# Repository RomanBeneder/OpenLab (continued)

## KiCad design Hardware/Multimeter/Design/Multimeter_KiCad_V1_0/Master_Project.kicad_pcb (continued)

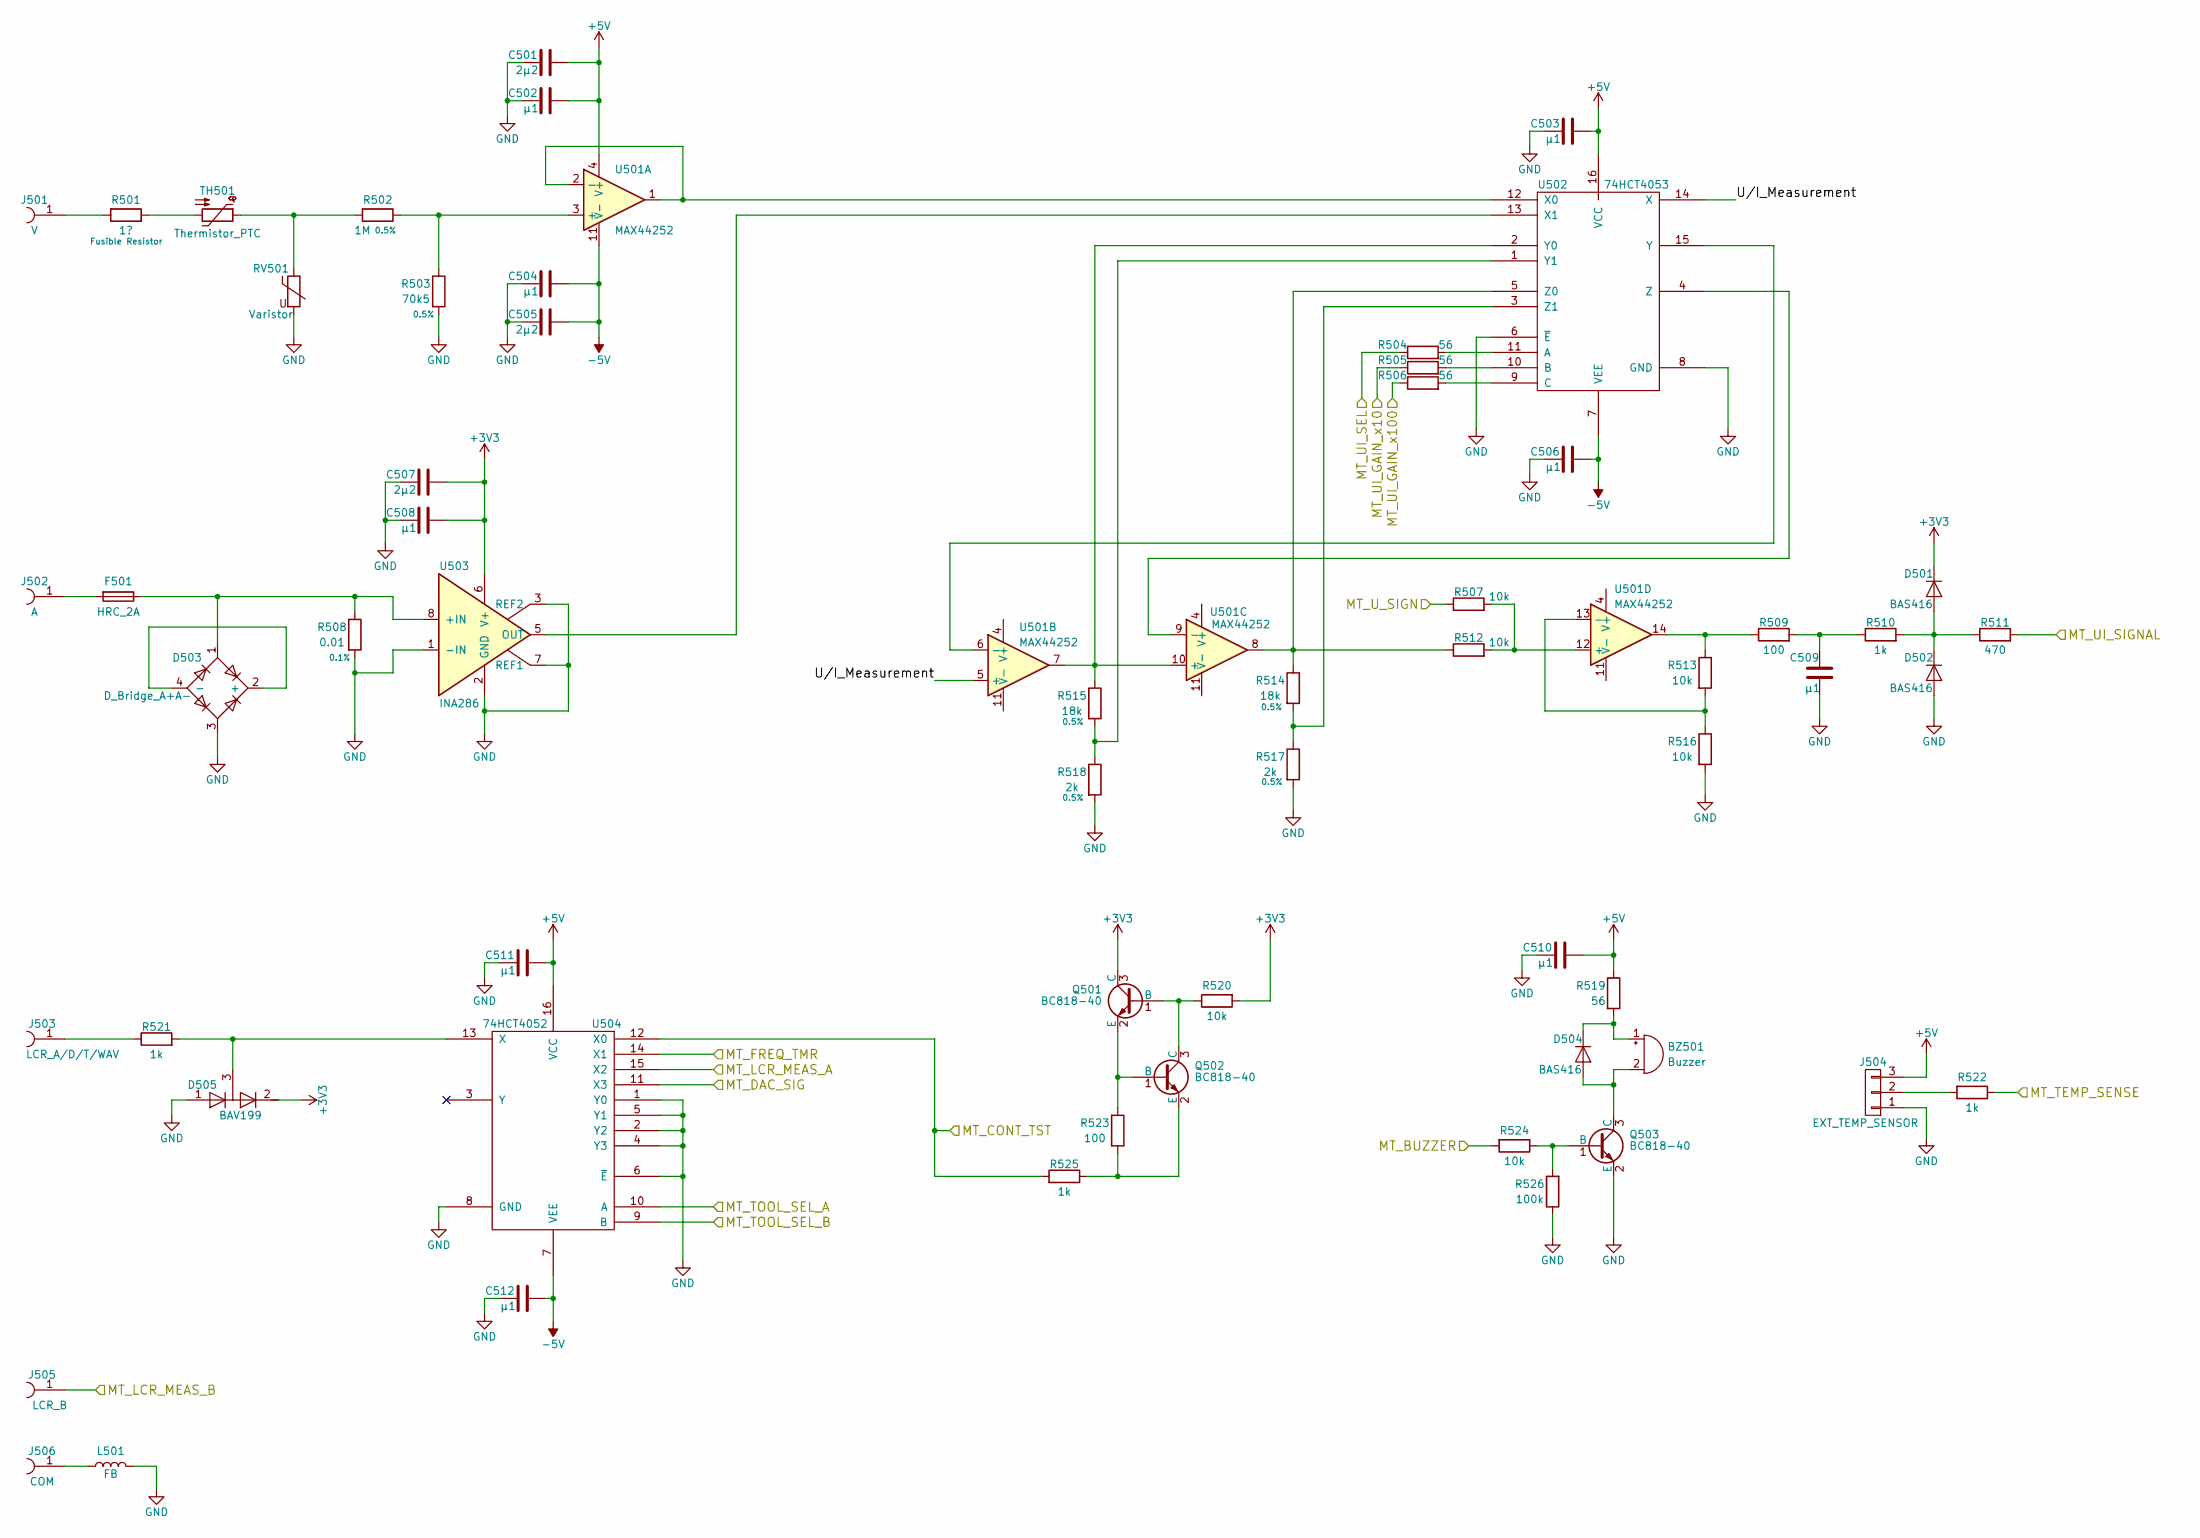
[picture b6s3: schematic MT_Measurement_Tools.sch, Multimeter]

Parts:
BZ501: Buzzer; MagneticBuzzer_ProSignal_ABT-410-RC
C501, C505, C507: 2µ2; C_0603
C502, C503, C504, C506, C508, C509, C510, C511, C512: µ1; C_0603
D501, D502, D504: BAS416; D_SOD-323
D503: D_Bridge_A+A-; Diode_Bridge_Round_D8.9mm
D505: BAV199; SOT-23
F501: HRC_2A; Fuseholder5x20_horiz_open_Schurter_0031_8201
J501: V; Banana_Jack_1Pin
J502: A; Banana_Jack_1Pin
J503: LCR_A/D/T/WAV; Banana_Jack_1Pin
J504: EXT_TEMP_SENSOR; Pin_Header_Straight_1x03_Pitch2.54mm
J505: LCR_B; Banana_Jack_1Pin
J506: COM; Banana_Jack_1Pin
L501: FB; R_0805
Q501, Q502, Q503: BC818-40; SOT-23
R501: 1?; R_Axial_DIN0207_L6.3mm_D2.5mm_P15.24mm_Horizontal
R502: 1M; R_0805; Toleranz 0.5%
R503: 70k5; R_0805; Toleranz 0.5%
R504, R505, R506, R519: 56; R_0603
R507, R512, R516, R520, R524: 10k; R_0603
R508: 0.01; R_4320; Toleranz 0.1%
R509, R523: 100; R_0603
R510, R521, R522, R525: 1k; R_0603
R511: 470; R_0603
R513: 10k; R_0603; Toleranz 1%
R514, R515: 18k; R_0603; Toleranz 0.5%
R517, R518: 2k; R_0603; Toleranz 0.5%
R526: 100k; R_0603
RV501: Varistor; RV_Disc_D7_W5.5_P5
TH501: Thermistor_PTC; R_Box_L14.4mm_W2.5mm_P5.08mm
U501: MAX44252; SOIC-14_3.9x8.7mm_Pitch1.27mm
U502: 74HCT4053; TSSOP-16_4.4x5mm_Pitch0.65mm
U503: INA286; SOIC-8_3.9x4.9mm_Pitch1.27mm
U504: 74HCT4052; TSSOP-16_4.4x5mm_Pitch0.65mm

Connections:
+3V3: C507.1, C508.1, D501.1 (K), D505.2 (K), Q501.3 (C), R520.2, U503.6 (V+); also elsewhere on the board
+5V: C501.1, C502.1, C503.1, C510.1, C511.1, J504.3, R519.1, U501.4 (V+), U502.16 (VCC), U504.16 (VCC); also elsewhere on the board
-5V: C504.1, C505.1, C506.1, C512.1, U501.11 (V-), U502.7 (VEE), U504.7 (VEE); also elsewhere on the board
/MT Measurement Tools/U/I_Measurement: U501.5 (+), U502.14 (X)
/TLD_BUZZER: R524.2; also elsewhere on the board
/TLD_CONT_TST: R525.2, U504.12 (X0); also elsewhere on the board
/TLD_DAC_SIG: U504.11 (X3); also elsewhere on the board
/TLD_FREQ_TMR: U504.14 (X1); also elsewhere on the board
/TLD_LCR_MEAS_A: U504.15 (X2); also elsewhere on the board
/TLD_LCR_MEAS_B: J505.1; also elsewhere on the board
/TLD_TEMP_SENSE: R522.1; also elsewhere on the board
/TLD_TOOL_SEL_A: U504.10 (A); also elsewhere on the board
/TLD_TOOL_SEL_B: U504.9 (B); also elsewhere on the board
/TLD_UI_GAIN_x10: R505.1; also elsewhere on the board
/TLD_UI_GAIN_x100: R506.1; also elsewhere on the board
/TLD_UI_SEL: R504.1; also elsewhere on the board
/TLD_UI_SIGNAL: R511.2; also elsewhere on the board
/TLD_U_SIGN: R507.1; also elsewhere on the board
GND: C501.2, C502.2, C503.2, C504.2, C505.2, C506.2, C507.2, C508.2, C509.1, C510.2, C511.2, C512.2, D502.2 (A), D503.3, D505.1 (A), J504.1, L501.2, Q503.2 (E), R503.2, R508.2, R516.2, R517.2, R518.2, R526.1, RV501.2, U502.6 (~E~), U502.8 (GND), U503.1 (-IN), U503.2 (GND), U503.3 (REF2), U503.7 (REF1), U504.1 (Y0), U504.2 (Y2), U504.4 (Y3), U504.5 (Y1), U504.6 (~E~), U504.8 (GND); also elsewhere on the board
unnamed: BZ501.1 (-), D504.1 (K), R519.2
unnamed: BZ501.2 (+), D504.2 (A), Q503.3 (C)
unnamed: C509.2, R509.2, R510.1
unnamed: D501.2 (A), D502.1 (K), R510.2, R511.1
unnamed: D503.1, F501.1, R508.1, U503.8 (+IN)
unnamed: D503.2 (+), D503.4 (-)
unnamed: D505.3 (common), R521.2, U504.13 (X)
unnamed: F501.2, J502.1
unnamed: J501.1, R501.2
unnamed: J503.1, R521.1
unnamed: J504.2, R522.2
unnamed: J506.1, L501.1
unnamed: Q501.1 (B), Q502.3 (C), R520.1
unnamed: Q501.2 (E), Q502.1 (B), R523.2
unnamed: Q502.2 (E), R523.1, R525.1
unnamed: Q503.1 (B), R524.1, R526.2
unnamed: R501.1, TH501.2
unnamed: R502.1, R503.1, U501.3 (+)
unnamed: R502.2, RV501.1, TH501.1
unnamed: R504.2, U502.11 (A)
unnamed: R505.2, U502.10 (B)
unnamed: R506.2, U502.9 (C)
unnamed: R507.2, R512.2, U501.12 (+)
unnamed: R509.1, R513.1, U501.14
unnamed: R512.1, R514.1, U501.8, U502.5 (Z0)
unnamed: R513.2, R516.1, U501.13 (-)
unnamed: R514.2, R517.1, U502.3 (Z1)
unnamed: R515.1, U501.7, U501.10 (+), U502.2 (Y0)
unnamed: R515.2, R518.1, U502.1 (Y1)
unnamed: U501.1, U501.2 (-), U502.12 (X0)
unnamed: U501.6 (-), U502.15 (Y)
unnamed: U501.9 (-), U502.4 (Z)
unnamed: U502.13 (X1), U503.5 (OUT)

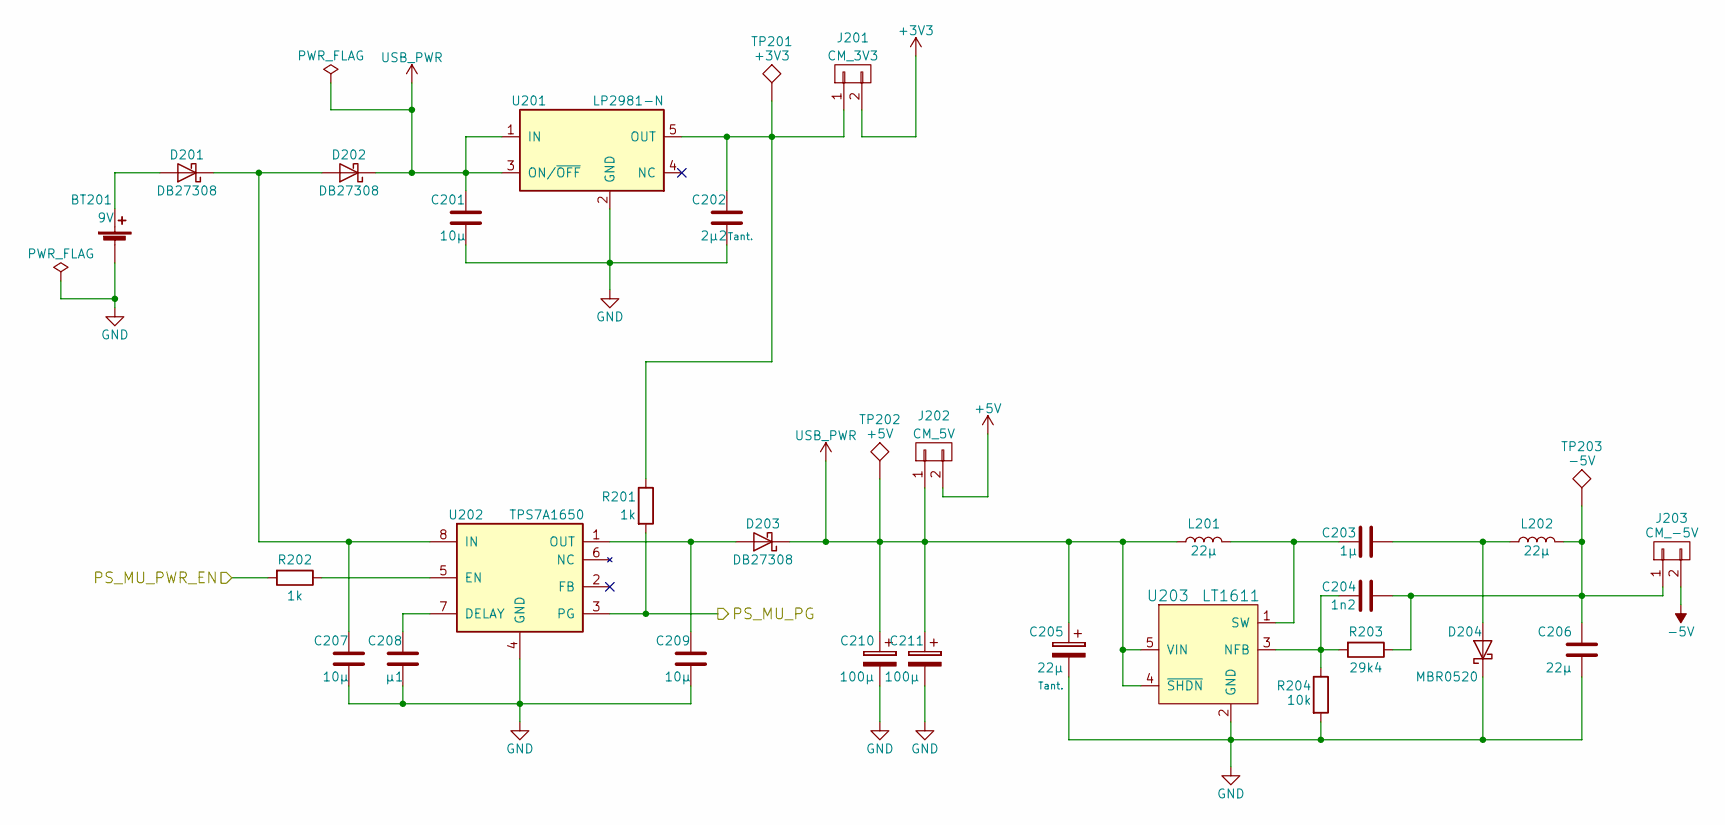
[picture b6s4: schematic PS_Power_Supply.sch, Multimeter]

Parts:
BT201: 9V; Pin_Header_Straight_1x02_Pitch2.54mm
C201, C207, C209: 10µ; C_1206
C202: 2µ2; C_1206
C203: 1µ; C_0603
C204: 1n2; C_0603
C205, C206: 22µ; C_1206
C208: µ1; C_0603
C210, C211: 100µ; CP_Elec_6.3x5.7
D201, D202, D203: DB27308; D_0603
D204: MBR0520; D_SOD-123
J201: CM_3V3; Pin_Header_Straight_1x02_Pitch2.54mm
J202: CM_5V; Pin_Header_Straight_1x02_Pitch2.54mm
J203: CM_-5V; Pin_Header_Straight_1x02_Pitch2.54mm
L201, L202: 22µ; Inductor_Taiyo-Yuden_MD-4040
R201, R202: 1k; R_0603
R203: 29k4; R_0603
R204: 10k; R_0603
TP201: +3V3; Measurement_Point_Square-SMD-Pad_Small
TP202: +5V; Measurement_Point_Square-SMD-Pad_Small
TP203: -5V; Measurement_Point_Square-SMD-Pad_Small
U201: LP2981-N; SOT-23-5
U202: TPS7A1650; TSSOP-8_3x3mm_Pitch0.65mm
U203: LT1611; SOT-23-5

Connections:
+3V3: J201.2; also elsewhere on the board
+5V: J202.2; also elsewhere on the board
-5V: J203.2; also elsewhere on the board
/TLD_MU_PG: R201.2, U202.3 (PG); also elsewhere on the board
/TLD_MU_PWR_EN: R202.2; also elsewhere on the board
GND: BT201.2 (-), C201.2, C202.2, C205.2, C206.1, C207.2, C208.2, C209.2, C210.2, C211.2, D204.1 (K), R204.2, U201.2 (GND), U202.4 (GND), U203.2 (GND); also elsewhere on the board
unnamed: BT201.1 (+), D201.2 (A)
unnamed: C202.1, J201.1, R201.1, TP201.1, U201.5 (OUT)
unnamed: C203.1, D204.2 (A), L202.1
unnamed: C203.2, L201.2, U203.1 (SW)
unnamed: C204.1, C206.2, J203.1, L202.2, R203.1, TP203.1
unnamed: C204.2, R203.2, R204.1, U203.3 (NFB)
unnamed: C207.1, D201.1 (K), D202.2 (A), U202.8 (IN)
unnamed: C208.1, U202.7 (DELAY)
unnamed: C209.1, D203.2 (A), U202.1 (OUT)
unnamed: R202.1, U202.5 (EN)
USB_PWR: C201.1, C205.1, C210.1, C211.1, D202.1 (K), D203.1 (K), J202.1, L201.1, TP202.1, U201.1 (IN), U201.3 (ON/~OFF~), U203.4 (~SHDN~), U203.5 (VIN); also elsewhere on the board

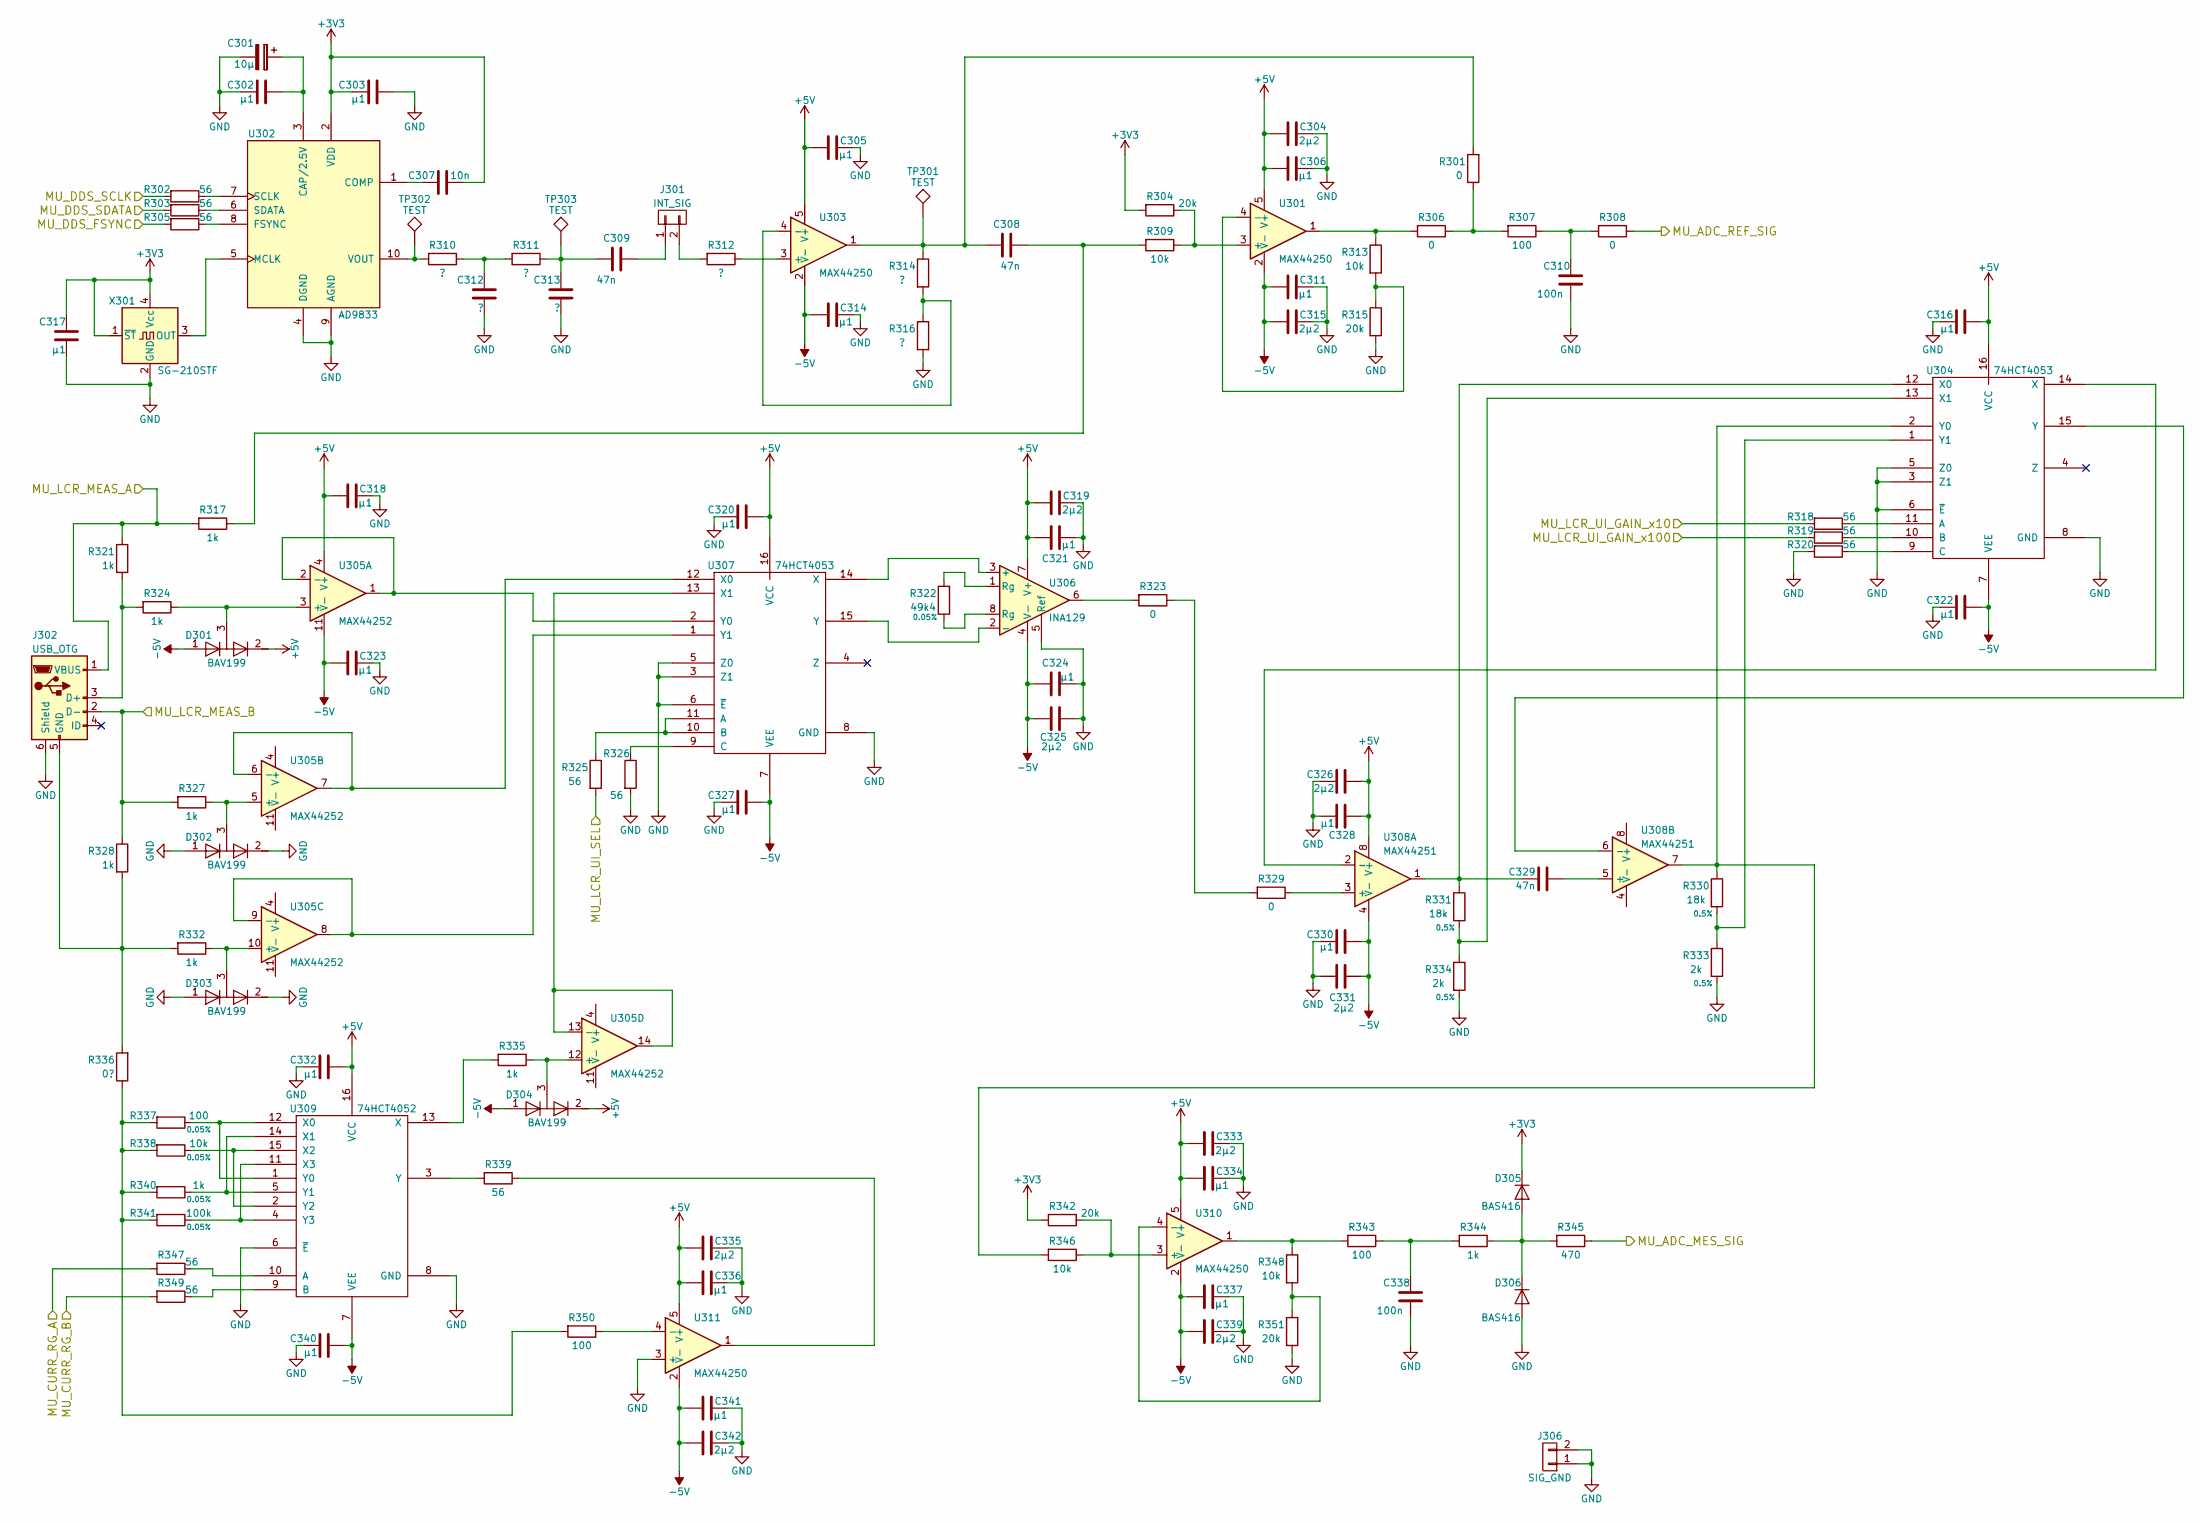
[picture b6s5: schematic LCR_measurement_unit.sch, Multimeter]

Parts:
C301: 10µ; CP_Elec_4x5.7
C302, C303, C305, C306, C311, C314, C316, C317, C318, C320, C321, C322, C323, C324, C327, C328, C330, C332, C334, C336, C337, C340, C341: µ1; C_0603
C304, C315, C319, C325, C326, C331, C333, C335, C339, C342: 2µ2; C_0603
C307: 10n; C_0603
C308, C309, C329: 47n; C_0603
C310, C338: 100n; C_0603
C312, C313: ?; C_0603
D301, D302, D303, D304: BAV199; SOT-23
D305, D306: BAS416; D_SOD-323
J301: INT_SIG; Pin_Header_Straight_1x02_Pitch2.54mm
J302: USB_OTG; USB_Micro_B
J306: SIG_GND; Pin_Header_Straight_1x02_Pitch2.54mm
R301, R306, R308, R323, R329: 0; R_0603
R302, R303, R305, R318, R319, R320, R325, R326, R339, R347, R349: 56; R_0603
R304, R315, R342, R351: 20k; R_0603
R307, R343, R350: 100; R_0603
R309, R313, R346, R348: 10k; R_0603
R310, R311, R312, R314, R316: ?; R_0603
R317, R321, R324, R327, R328, R332, R335, R344: 1k; R_0603
R322: 49k4; R_0603; Toleranz 0.05%
R330, R331: 18k; R_0603; Toleranz 0.5%
R333, R334: 2k; R_0603; Toleranz 0.5%
R336: 0?; R_0603
R337: 100; R_0603; Toleranz 0.05%
R338: 10k; R_0603; Toleranz 0.05%
R340: 1k; R_0603; Toleranz 0.05%
R341: 100k; R_0603; Toleranz 0.05%
R345: 470; R_0603
TP301, TP302, TP303: TEST; Measurement_Point_Square-SMD-Pad_Small
U301, U303, U310, U311: MAX44250; SOT-23-5
U302: AD9833; MSOP-10_3x3mm_Pitch0.5mm
U304, U307: 74HCT4053; TSSOP-16_4.4x5mm_Pitch0.65mm
U305: MAX44252; SOIC-14_3.9x8.7mm_Pitch1.27mm
U306: INA129; SOIC-8_3.9x4.9mm_Pitch1.27mm
U308: MAX44251; TSSOP-8_3x3mm_Pitch0.65mm
U309: 74HCT4052; TSSOP-16_4.4x5mm_Pitch0.65mm
X301: SG-210STF; Oscillator_SMD_SeikoEpson_SG210-4pin_2.5x2.0mm

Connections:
+3V3: C303.1, C307.2, C317.2, D305.1 (K), R304.2, R342.2, U302.2 (VDD), X301.1 (~ST~), X301.4 (Vcc); also elsewhere on the board
+5V: C304.1, C305.1, C306.1, C316.1, C318.1, C319.1, C320.1, C321.1, C326.1, C328.1, C332.1, C333.1, C334.1, C335.1, C336.1, D301.2 (K), D304.2 (K), U301.5 (V+), U303.5 (V+), U304.16 (VCC), U305.4 (V+), U306.7 (V+), U307.16 (VCC), U308.8 (V+), U309.16 (VCC), U310.5 (V+), U311.5 (V+); also elsewhere on the board
-5V: C311.1, C314.1, C315.1, C322.1, C323.1, C324.1, C325.1, C327.1, C330.1, C331.1, C337.1, C339.1, C340.1, C341.1, C342.1, D301.1 (A), D304.1 (A), U301.2 (V-), U303.2 (V-), U304.7 (VEE), U305.11 (V-), U306.4 (V-), U307.7 (VEE), U308.4 (V-), U309.7 (VEE), U310.2 (V-), U311.2 (V-); also elsewhere on the board
/TLD_ADC_MED_SIG: R345.1; also elsewhere on the board
/TLD_ADC_REF_SIG: R308.1; also elsewhere on the board
/TLD_CURR_RG_A: R347.2; also elsewhere on the board
/TLD_CURR_RG_B: R349.2; also elsewhere on the board
/TLD_DDS_FSYNC: R305.2; also elsewhere on the board
/TLD_DDS_SCLK: R302.2; also elsewhere on the board
/TLD_DDS_SDATA: R303.2; also elsewhere on the board
/TLD_LCR_MEAS_A: J302.1 (VBUS), R317.2, R321.1; also elsewhere on the board
/TLD_LCR_MEAS_B: J302.2 (D-), R327.2, R328.1; also elsewhere on the board
/TLD_LCR_UI_GAIN_x10: R318.2; also elsewhere on the board
/TLD_LCR_UI_GAIN_x100: R319.2; also elsewhere on the board
/TLD_LCR_UI_SEL: R325.2; also elsewhere on the board
GND: C301.2, C302.1, C303.2, C304.2, C305.2, C306.2, C310.1, C311.2, C312.1, C313.1, C314.2, C315.2, C316.2, C317.1, C318.2, C319.2, C320.2, C321.2, C322.2, C323.2, C324.2, C325.2, C326.2, C327.2, C328.2, C330.2, C331.2, C332.2, C333.2, C334.2, C335.2, C336.2, C337.2, C338.1, C339.2, C340.2, C341.2, C342.2, D302.1 (A), D302.2 (K), D303.1 (A), D303.2 (K), D306.2 (A), J302.6 (Shield), J306.1, J306.2, R315.2, R316.2, R320.2, R326.2, R333.2, R334.2, R351.2, U302.4 (DGND), U302.9 (AGND), U304.3 (Z1), U304.5 (Z0), U304.6 (~E~), U304.8 (GND), U306.5 (Ref), U307.3 (Z1), U307.5 (Z0), U307.6 (~E~), U307.8 (GND), U309.6 (~E~), U309.8 (GND), U311.3 (+), X301.2 (GND); also elsewhere on the board
unnamed: C301.1, C302.2, U302.3 (CAP/2.5V)
unnamed: C307.1, U302.1 (COMP)
unnamed: C308.1, R301.2, R314.1, TP301.1, U303.1
unnamed: C308.2, R309.2, R317.1
unnamed: C309.1, C313.2, R311.1, TP303.1
unnamed: C309.2, J301.1
unnamed: C310.2, R307.1, R308.2
unnamed: C312.2, R310.1, R311.2
unnamed: C329.1, U308.5 (+)
unnamed: C329.2, R331.1, U304.12 (X0), U308.1
unnamed: C338.2, R343.1, R344.2
unnamed: D301.3 (common), R324.1, U305.3 (+)
unnamed: D302.3 (common), R327.1, U305.5 (+)
unnamed: D303.3 (common), R332.1, U305.10 (+)
unnamed: D304.3 (common), R335.1, U305.12 (+)
unnamed: D305.2 (A), D306.1 (K), R344.1, R345.2
unnamed: J301.2, R312.2
unnamed: J302.3 (D+), R321.2, R324.2
unnamed: J302.5 (GND), R328.2, R332.2, R336.2
unnamed: R301.1, R306.1, R307.2
unnamed: R302.1, U302.7 (SCLK)
unnamed: R303.1, U302.6 (SDATA)
unnamed: R304.1, R309.1, U301.3 (+)
unnamed: R305.1, U302.8 (FSYNC)
unnamed: R306.2, R313.1, U301.1
unnamed: R310.2, TP302.1, U302.10 (VOUT)
unnamed: R312.1, U303.3 (+)
unnamed: R313.2, R315.1, U301.4 (-)
unnamed: R314.2, R316.1, U303.4 (-)
unnamed: R318.1, U304.11 (A)
unnamed: R319.1, U304.10 (B)
unnamed: R320.1, U304.9 (C)
unnamed: R322.1, U306.8 (Rg)
unnamed: R322.2, U306.1 (Rg)
unnamed: R323.1, R329.2
unnamed: R323.2, U306.6
unnamed: R325.1, U307.10 (B), U307.11 (A)
unnamed: R326.1, U307.9 (C)
unnamed: R329.1, U308.3 (+)
unnamed: R330.1, R346.2, U304.2 (Y0), U308.7
unnamed: R330.2, R333.1, U304.1 (Y1)
unnamed: R331.2, R334.1, U304.13 (X1)
unnamed: R335.2, U309.13 (X)
unnamed: R336.1, R337.2, R338.2, R340.2, R341.2, R350.2
unnamed: R337.1, U309.1 (Y0), U309.12 (X0)
unnamed: R338.1, U309.2 (Y2), U309.15 (X2)
unnamed: R339.1, U311.1
unnamed: R339.2, U309.3 (Y)
unnamed: R340.1, U309.5 (Y1), U309.14 (X1)
unnamed: R341.1, U309.4 (Y3), U309.11 (X3)
unnamed: R342.1, R346.1, U310.3 (+)
unnamed: R343.2, R348.1, U310.1
unnamed: R347.1, U309.10 (A)
unnamed: R348.2, R351.1, U310.4 (-)
unnamed: R349.1, U309.9 (B)
unnamed: R350.1, U311.4 (-)
unnamed: U302.5 (MCLK), X301.3 (OUT)
unnamed: U304.14 (X), U308.2 (-)
unnamed: U304.15 (Y), U308.6 (-)
unnamed: U305.1, U305.2 (-), U307.2 (Y0)
unnamed: U305.6 (-), U305.7, U307.12 (X0)
unnamed: U305.8, U305.9 (-), U307.1 (Y1)
unnamed: U305.13 (-), U305.14, U307.13 (X1)
unnamed: U306.2 (-), U307.15 (Y)
unnamed: U306.3 (+), U307.14 (X)

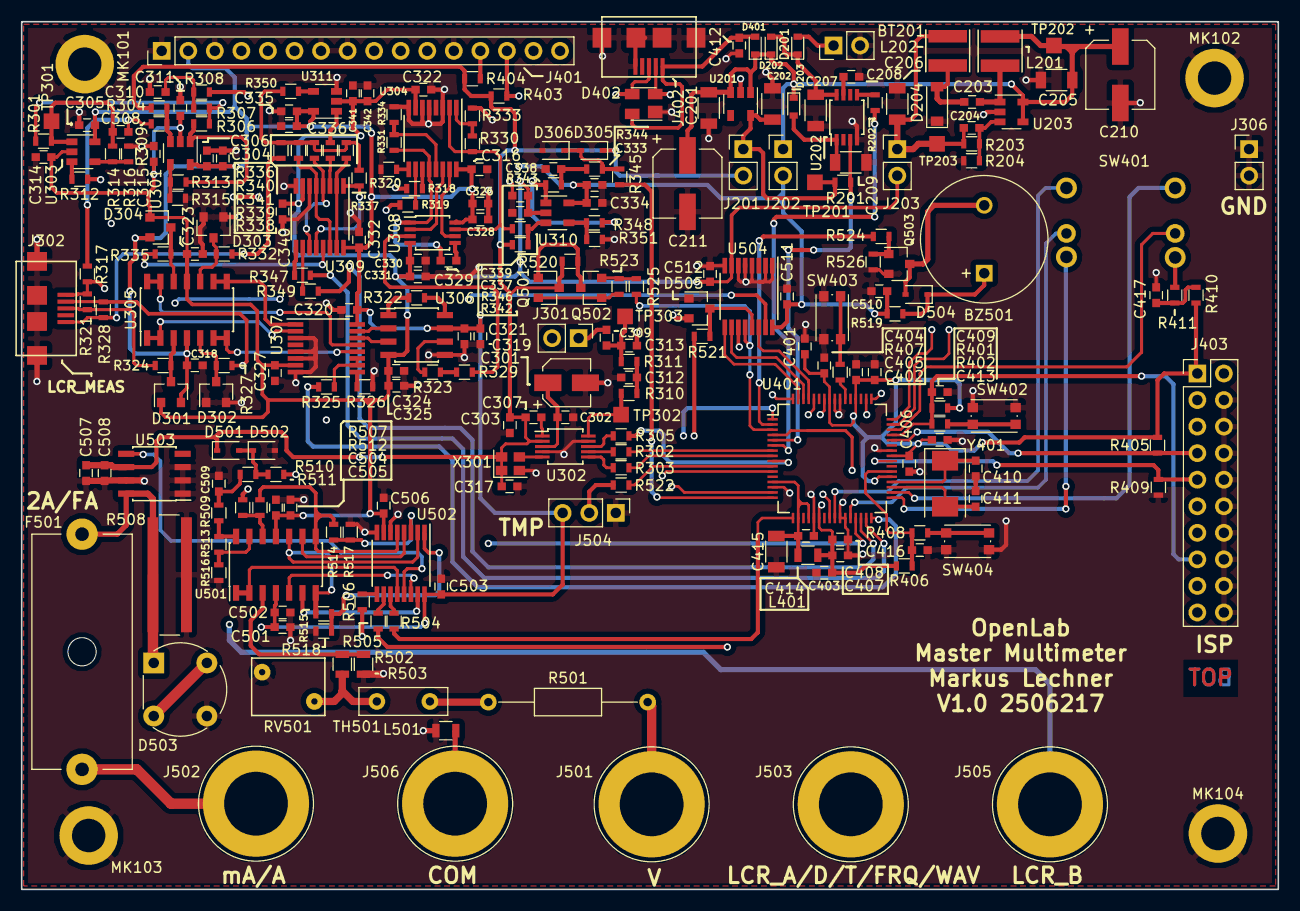
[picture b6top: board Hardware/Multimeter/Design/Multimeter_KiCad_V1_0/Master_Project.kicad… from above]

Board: 4 copper layers, 120.2 x 83.0 mm, 253 parts (0 on the bottom side), 164 nets.
